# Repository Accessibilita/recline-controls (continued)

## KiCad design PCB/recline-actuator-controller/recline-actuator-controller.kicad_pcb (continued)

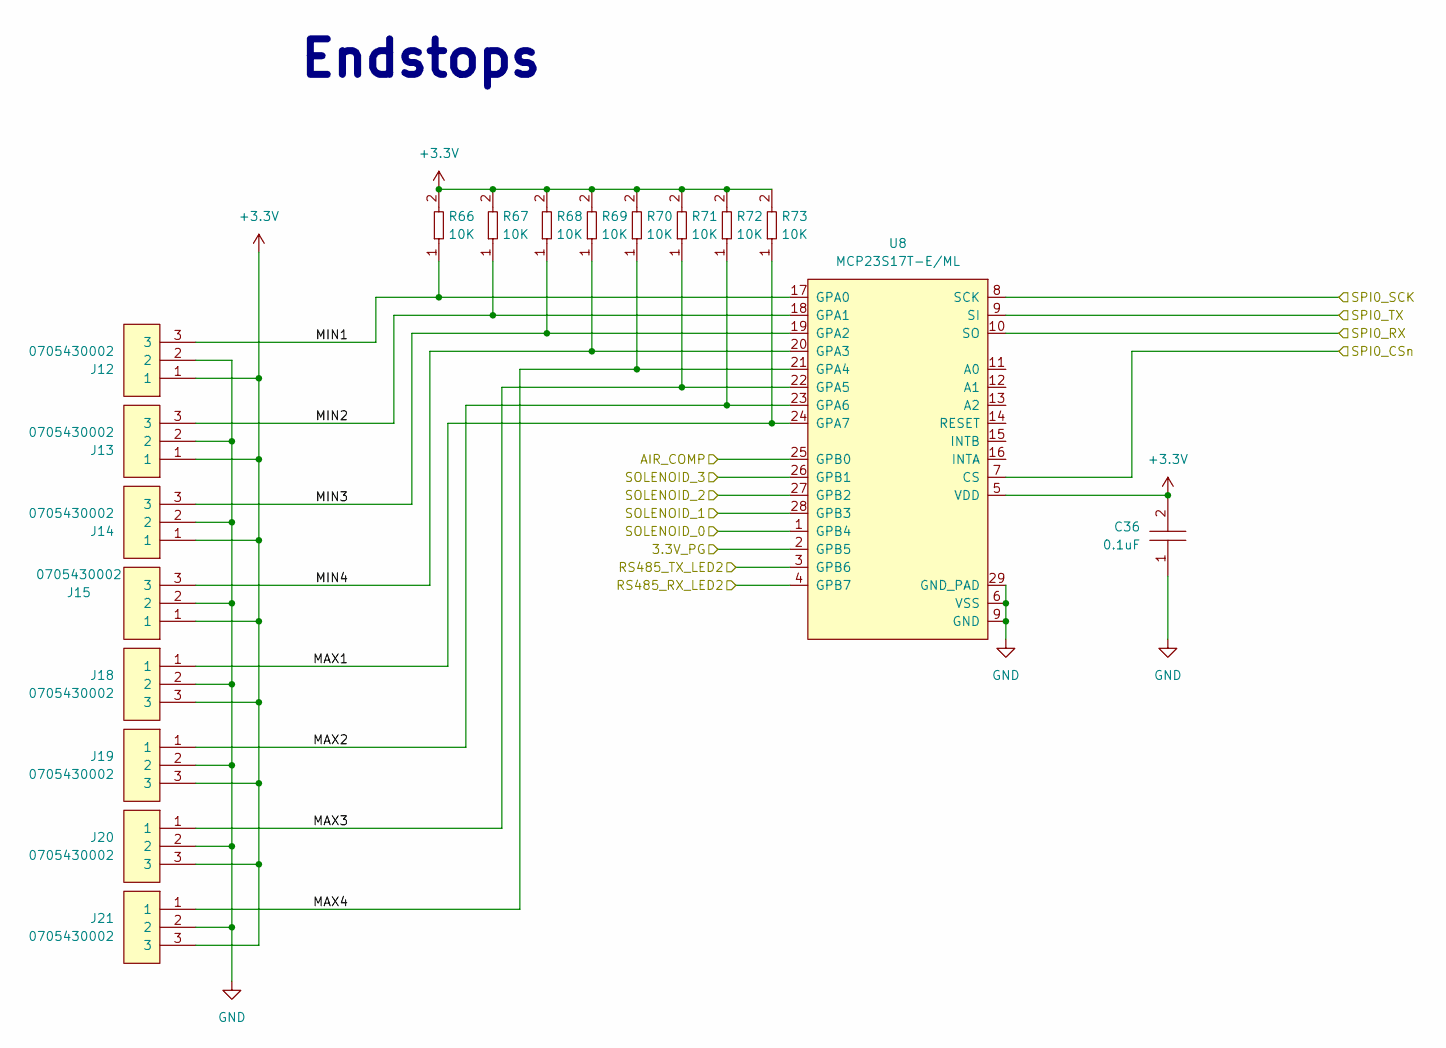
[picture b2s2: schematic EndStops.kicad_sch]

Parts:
C36: C0402C104K9PACTU; R0402; Tolerance 10%; Voltage 6.3V; MFR# C0402C104K9PACTU
J12, J13, J14, J15, J18, J19, J20, J21: 0705430002; Shrouded_Pin_Header_Straight_1x03_Pitch2.54mm; Tolerance *; Voltage 250V; MFR# 0705430002
R66, R67, R68, R69, R70, R71, R72, R73: RC0402FR-0710KL; R0402; Tolerance 1%; Voltage *; MFR# RC0402FR-0710KL
U8: MCP23S17T-E/ML; QFN28_6x6MC_MCH-L; Tolerance *; Voltage 1.8V-5.5V; MFR# MCP23S17T-E/ML

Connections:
+3.3V: C36.2, J12.1, J13.1, J14.1, J15.1, J18.3, J19.3, J20.3, J21.3, R66.2, R67.2, R68.2, R69.2, R70.2, R71.2, R72.2, R73.2, U8.5 (VDD); also elsewhere on the board
/End Stop Limit Switches/AIR_COMP: U8.25 (GPB0); also elsewhere on the board
/End Stop Limit Switches/MAX1: J18.1, R73.1, U8.24 (GPA7)
/End Stop Limit Switches/MAX2: J19.1, R72.1, U8.23 (GPA6)
/End Stop Limit Switches/MAX3: J20.1, R71.1, U8.22 (GPA5)
/End Stop Limit Switches/MAX4: J21.1, R70.1, U8.21 (GPA4)
/End Stop Limit Switches/MIN1: J12.3, R66.1, U8.17 (GPA0)
/End Stop Limit Switches/MIN2: J13.3, R67.1, U8.18 (GPA1)
/End Stop Limit Switches/MIN3: J14.3, R68.1, U8.19 (GPA2)
/End Stop Limit Switches/MIN4: J15.3, R69.1, U8.20 (GPA3)
/End Stop Limit Switches/RS485_RX_LED2: U8.4 (GPB7); also elsewhere on the board
/End Stop Limit Switches/RS485_TX_LED2: U8.3 (GPB6); also elsewhere on the board
/End Stop Limit Switches/SOLENOID_0: U8.1 (GPB4); also elsewhere on the board
/End Stop Limit Switches/SOLENOID_1: U8.28 (GPB3); also elsewhere on the board
/End Stop Limit Switches/SOLENOID_2: U8.27 (GPB2); also elsewhere on the board
/End Stop Limit Switches/SOLENOID_3: U8.26 (GPB1); also elsewhere on the board
/Power/3.3V_PG: U8.2 (GPB5); also elsewhere on the board
/RP2040/SPI0_CSn: U8.7 (CS); also elsewhere on the board
/RP2040/SPI0_RX: U8.10 (SO); also elsewhere on the board
/RP2040/SPI0_SCK: U8.8 (SCK); also elsewhere on the board

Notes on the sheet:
Endstops

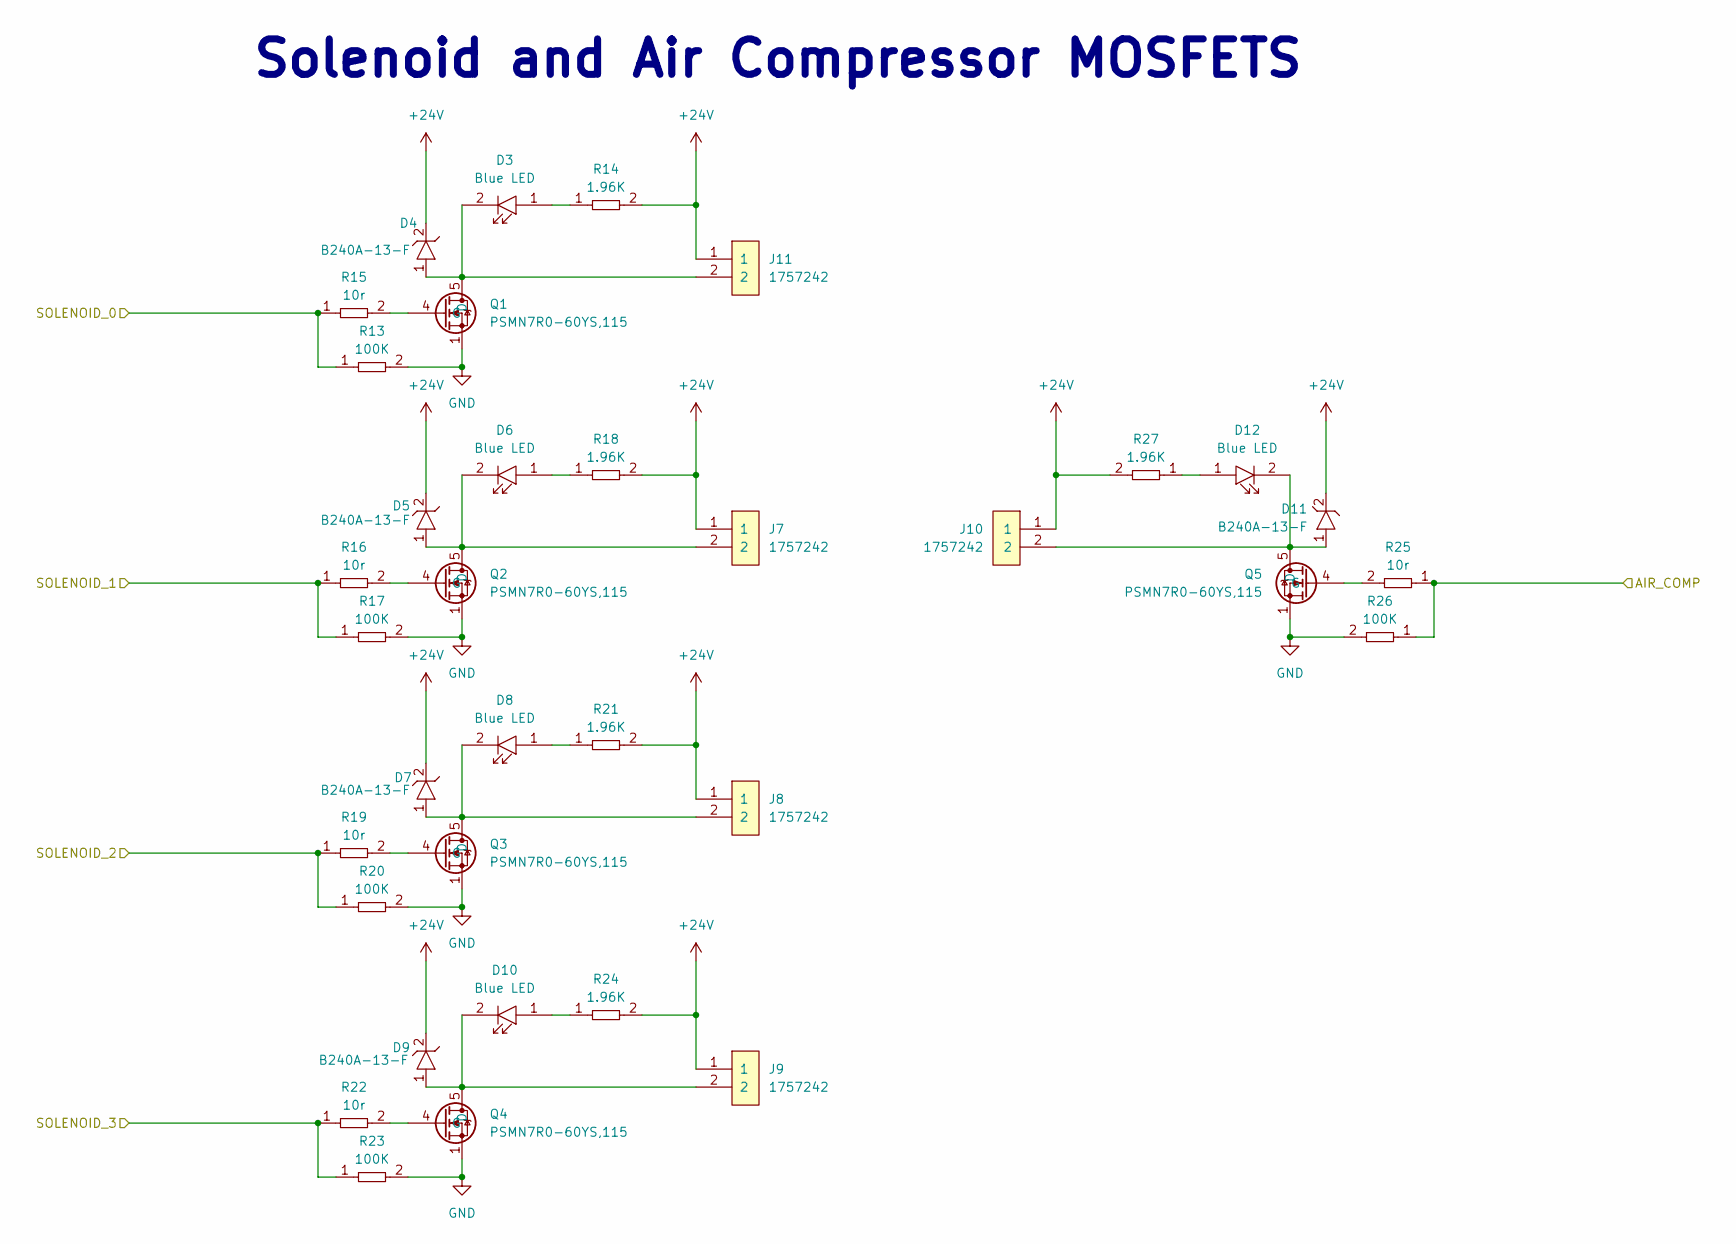
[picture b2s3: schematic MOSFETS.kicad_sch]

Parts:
D3, D6, D8, D10, D12: LTST-C194TBKT; LED0603; Tolerance *; Voltage 3.3V; MFR# LTST-C194TBKT
D4, D5, D7, D9, D11: B240A-13-F; Tolerance *; Voltage 40V; MFR# B240A-13-F
J7, J8, J9, J10, J11: 1757242; PhoenixContact_MSTBA-G_02x5.08mm_Angled; Tolerance *; Voltage 300V; MFR# 1757242
Q1, Q2, Q3, Q4, Q5: PSMN7R0-60YS,115; IC5_PSMN7R0-60YS_115_NEX-L; Tolerance *; Voltage 60V; MFR# PSMN7R0-60YS,115
R13, R17, R20, R23, R26: RC0805FR-07100KL; R0805; Tolerance 1%; Voltage *; MFR# RC0805FR-07100KL
R14, R18, R21, R24, R27: RC0805FR-071K96L; R0805; Tolerance 1%; Voltage N/A; MFR# RC0805FR-071K96L
R15, R16, R19, R22, R25: RC0805FR-0710RL; R0805; Tolerance 1%; Voltage *; MFR# RC0805FR-0710RL

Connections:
+24V: D4.2, D5.2, D7.2, D9.2, D11.2, J7.1, J8.1, J9.1, J10.1, J11.1, R14.2, R18.2, R21.2, R24.2, R27.2; also elsewhere on the board
/End Stop Limit Switches/AIR_COMP: R25.1, R26.1; also elsewhere on the board
/End Stop Limit Switches/SOLENOID_0: R13.1, R15.1; also elsewhere on the board
/End Stop Limit Switches/SOLENOID_1: R16.1, R17.1; also elsewhere on the board
/End Stop Limit Switches/SOLENOID_2: R19.1, R20.1; also elsewhere on the board
/End Stop Limit Switches/SOLENOID_3: R22.1, R23.1; also elsewhere on the board
unnamed: D3.1, R14.1
unnamed: D6.1, R18.1
unnamed: D8.1, R21.1
unnamed: D10.1, R24.1
unnamed: D12.1, R27.1
unnamed: D3.2, D4.1, J11.2, Q1.5 (D)
unnamed: Q1.4 (G), R15.2
unnamed: D5.1, D6.2, J7.2, Q2.5 (D)
unnamed: Q2.4 (G), R16.2
unnamed: D7.1, D8.2, J8.2, Q3.5 (D)
unnamed: Q3.4 (G), R19.2
unnamed: D9.1, D10.2, J9.2, Q4.5 (D)
unnamed: Q4.4 (G), R22.2
unnamed: D11.1, D12.2, J10.2, Q5.5 (D)
unnamed: Q5.4 (G), R25.2

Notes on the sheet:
Solenoid and Air Compressor MOSFETS

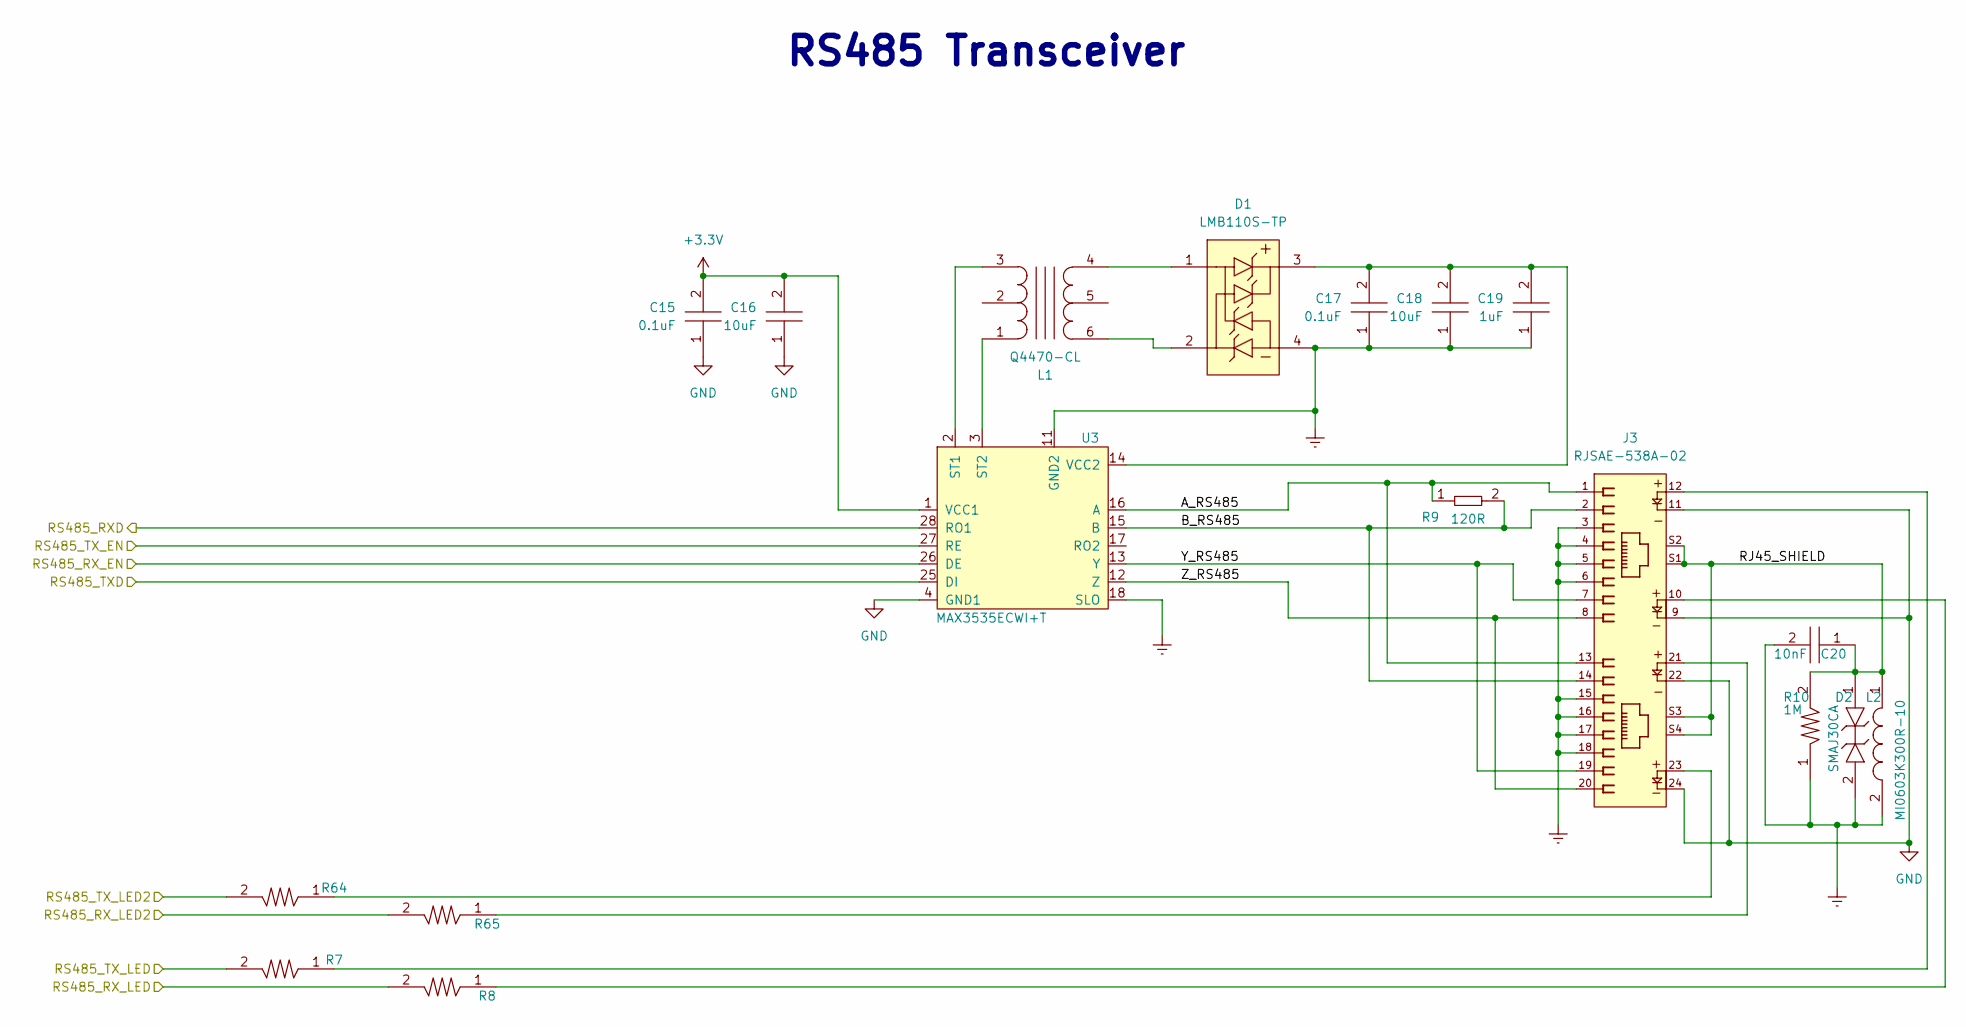
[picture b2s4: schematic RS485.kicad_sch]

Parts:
C15, C17: CL10B104JB8NNNC; C0603; Tolerance 5%; Voltage 50V; MFR# CL10B104JB8NNNC
C16, C18: CGA5L3X5R1V106K160AB; C1206; Tolerance 10%; Voltage 35V; MFR# CGA5L3X5R1V106K160AB
C19: C1206C105K3RACAUTO; D_SOD-123; Tolerance 10%; Voltage 25V; MFR# C1206C105K3RACAUTO
C20: C0805C103KCRACAUTO; C0805; Tolerance 10%; Voltage 500V; MFR# C0805C103KCRACAUTO
D1: LMB110S-TP; Tolerance *; Voltage 850 mV @ 500 mA; MFR# LMB110S-TP
D2: SMAJ30CA; Tolerance *; Voltage 30V Clamp; MFR# SMAJ30CA
J3: RJSAE-538A-02; AMPHENOL_RJSAE538A02; Tolerance N/A; Voltage *; MFR# RJSAE-538A-02
L1: Q4470-CL; SO6_Q4470-CL_C-SIZE_COC; Tolerance *; Voltage 5V; MFR# Q4470-CL
L2: MI0603K300R-10; Tolerance *; Voltage *; MFR# MI0603K300R-10
R7, R8, R64, R65: RC0603FR-07470RL; R0603; Tolerance 1%; Voltage *; MFR# RC0603FR-07470RL
R9: AC0402FR-07120RL; R0402; Tolerance 1%; Voltage *; MFR# AC0402FR-07120RL
R10: RC1206FR-071ML; R1206; Tolerance 1%; Voltage *; MFR# RC1206FR-071ML
U3: MAX3535ECWI+T; 21-0145_W28M&plus_9_MXM; Tolerance N/A; Voltage 3-5.5V; MFR# MAX3535ECWI+T

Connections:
+3.3V: C15.2, C16.2, U3.1 (VCC1); also elsewhere on the board
/End Stop Limit Switches/RS485_RX_LED2: R65.2; also elsewhere on the board
/End Stop Limit Switches/RS485_TX_LED2: R64.2; also elsewhere on the board
/RP2040/RS485_RXD: U3.28 (RO1); also elsewhere on the board
/RP2040/RS485_RX_EN: U3.26 (DE); also elsewhere on the board
/RP2040/RS485_RX_LED: R8.2; also elsewhere on the board
/RP2040/RS485_TXD: U3.25 (DI); also elsewhere on the board
/RP2040/RS485_TX_EN: U3.27 (RE); also elsewhere on the board
/RP2040/RS485_TX_LED: R7.2; also elsewhere on the board
/RS485 Transceiver/A_RS485: J3.1, J3.13, R9.1, U3.16 (A)
/RS485 Transceiver/B_RS485: J3.2, J3.14, R9.2, U3.15 (B)
/RS485 Transceiver/RJ45_SHIELD: C20.1, D2.1, J3.S1, J3.S2, J3.S3, J3.S4, L2.1, R10.2
/RS485 Transceiver/Y_RS485: J3.7, J3.19, U3.13 (Y)
/RS485 Transceiver/Z_RS485: J3.8, J3.20, U3.12 (Z)
Earth: C17.1, C18.1, C19.1, C20.2, D1.4, D2.2, J3.3, J3.4, J3.5, J3.6, J3.15, J3.16, J3.17, J3.18, L2.2, R10.1, U3.11 (GND2), U3.18 (SLO)
unnamed: D1.1, L1.4
unnamed: D1.2, L1.6
unnamed: J3.10, R8.1
unnamed: J3.12, R7.1
unnamed: J3.21, R65.1
unnamed: J3.23, R64.1
unnamed: L1.3, U3.2 (ST1)
unnamed: L1.1, U3.3 (ST2)
unnamed: C17.2, C18.2, C19.2, D1.3, U3.14 (VCC2)

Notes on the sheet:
RS485 Transceiver

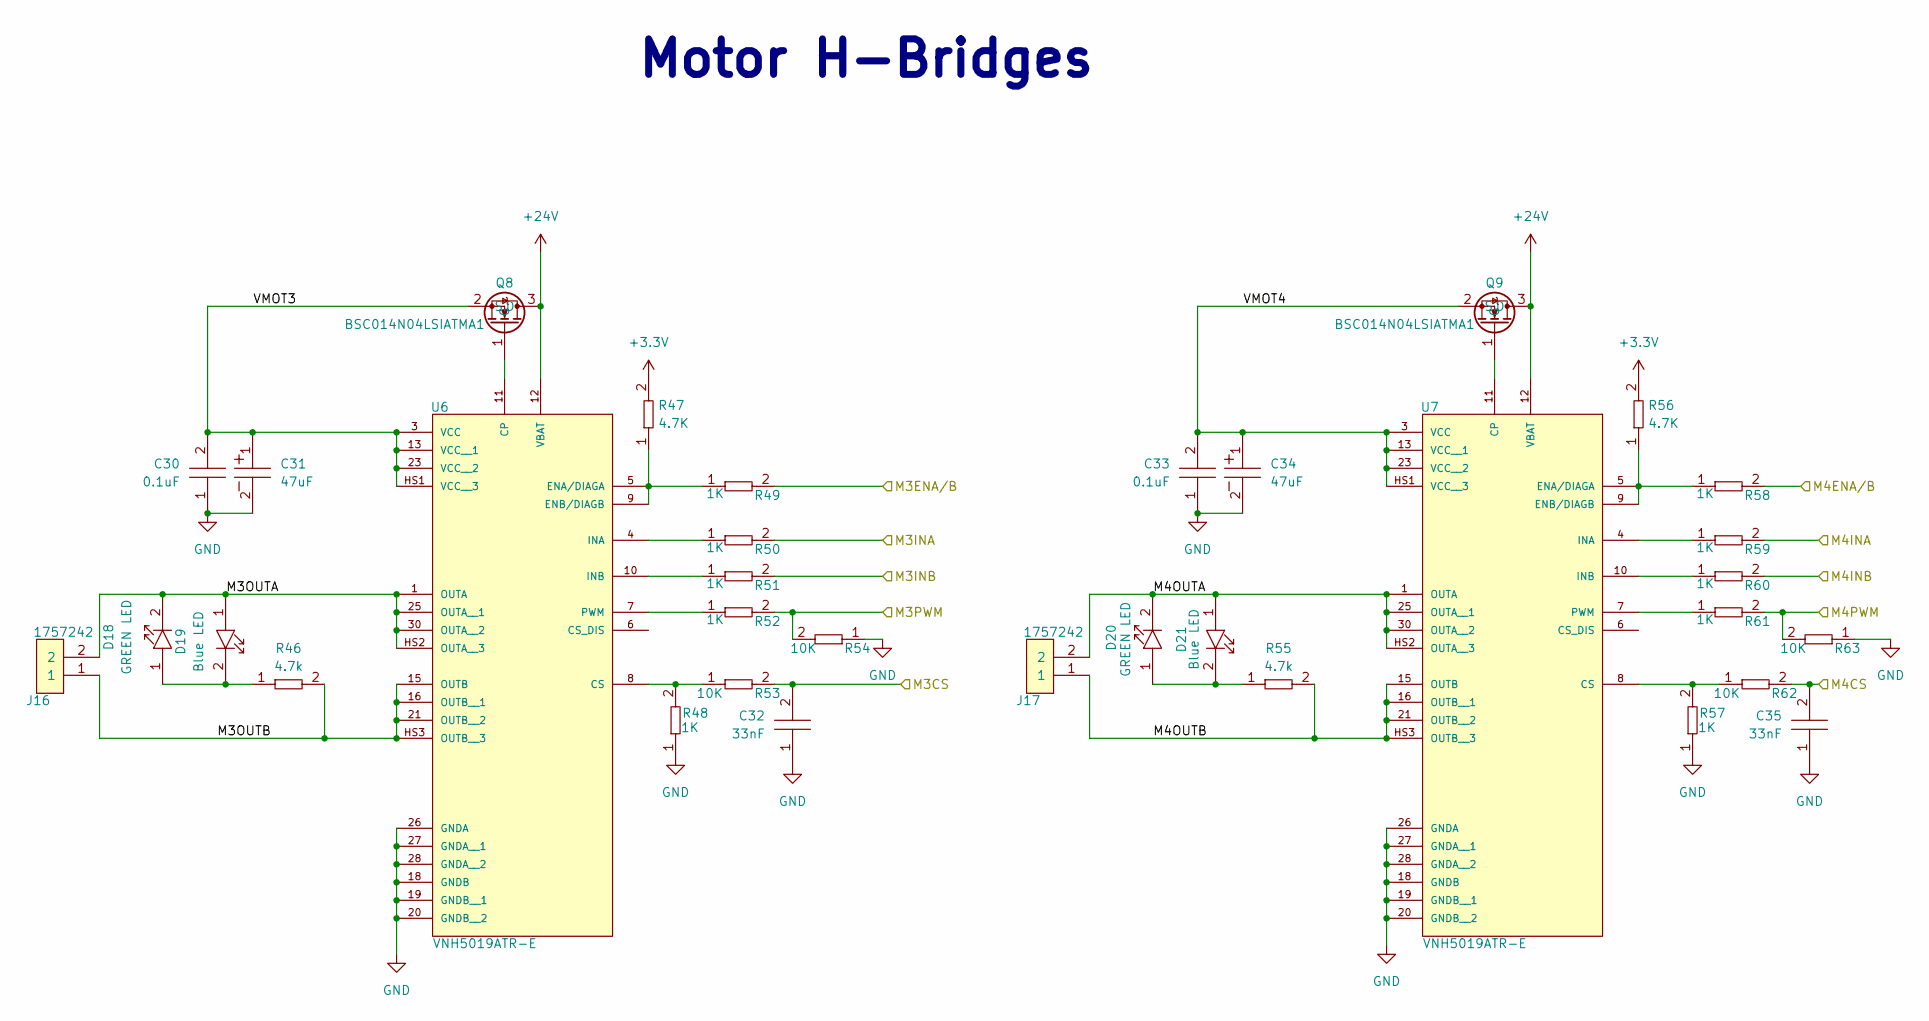
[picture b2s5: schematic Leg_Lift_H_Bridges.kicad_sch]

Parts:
C30, C33: CL21B104KBFNNNE; C0805; Tolerance 10%; Voltage 50V; MFR# Samsung Electro-Mechanics
C31, C34: UUQ1H470MCL1GS; CP_Elec_8x10; Tolerance 20%; Voltage 50V; MFR# UUQ1H470MCL1GS
C32, C35: C0402C333K4REC7867; C0402; Tolerance 10%; Voltage 16V; MFR# C0402C333K4REC7867
D18, D20: LTST-C194KGKT; LED0603; Tolerance *; Voltage 2.1V; MFR# LTST-C194KGKT
D19, D21: LTST-C194TBKT; LED0603; Tolerance *; Voltage 3.3V; MFR# LTST-C194TBKT
J16, J17: 1757242; PhoenixContact_MSTBA-G_02x5.08mm_Angled; Tolerance *; Voltage 300V; MFR# 1757242
Q8, Q9: BSC014N04LSIATMA1; PG-TDSON-8_INF; Tolerance N/A; Voltage 40V; MFR# BSC014N04LSIATMA1
R46, R55: RC0805FR-074K7L; R0805; Tolerance 1%; Voltage *; MFR# RC0805FR-074K7L
R47, R56: RC0402FR-074K7L; R0402; Tolerance 1%; Voltage *; MFR# RC0402FR-074K7L
R48, R49, R50, R51, R52, R57, R58, R59, R60, R61: RC0402FR-071KL; R0402; Tolerance 1%; Voltage *; MFR# RC0402FR-071KL
R53, R54, R62, R63: RC0402FR-0710KL; R0402; Tolerance 1%; Voltage *; MFR# RC0402FR-0710KL
U6, U7: VNH5019ATR-E; IC_VNH5019ATR-E; Tolerance *; Voltage 24; MFR# VNH5019ATR-E

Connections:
+3.3V: R47.2, R56.2; also elsewhere on the board
+24V: Q8.3 (D), Q9.3 (D), U6.12 (VBAT), U7.12 (VBAT); also elsewhere on the board
/Leg Lift Motors/M3CS: C32.2, R53.2; also elsewhere on the board
/Leg Lift Motors/M3ENA/B: R49.2; also elsewhere on the board
/Leg Lift Motors/M3INA: R50.2; also elsewhere on the board
/Leg Lift Motors/M3INB: R51.2; also elsewhere on the board
/Leg Lift Motors/M3OUTA: D18.2, D19.1, J16.2, U6.1 (OUTA), U6.25 (OUTA__1), U6.30 (OUTA__2), U6.HS2 (OUTA__3)
/Leg Lift Motors/M3OUTB: J16.1, R46.2, U6.15 (OUTB), U6.16 (OUTB__1), U6.21 (OUTB__2), U6.HS3 (OUTB__3)
/Leg Lift Motors/M3PWM: R52.2, R54.2; also elsewhere on the board
/Leg Lift Motors/M4CS: C35.2, R62.2; also elsewhere on the board
/Leg Lift Motors/M4ENA/B: R58.2; also elsewhere on the board
/Leg Lift Motors/M4INA: R59.2; also elsewhere on the board
/Leg Lift Motors/M4INB: R60.2; also elsewhere on the board
/Leg Lift Motors/M4OUTA: D20.2, D21.1, J17.2, U7.1 (OUTA), U7.25 (OUTA__1), U7.30 (OUTA__2), U7.HS2 (OUTA__3)
/Leg Lift Motors/M4OUTB: J17.1, R55.2, U7.15 (OUTB), U7.16 (OUTB__1), U7.21 (OUTB__2), U7.HS3 (OUTB__3)
/Leg Lift Motors/M4PWM: R61.2, R63.2; also elsewhere on the board
/Leg Lift Motors/VMOT3: C30.2, C31.1, Q8.2 (S), U6.3 (VCC), U6.13 (VCC__1), U6.23 (VCC__2), U6.HS1 (VCC__3)
/Leg Lift Motors/VMOT4: C33.2, C34.1, Q9.2 (S), U7.3 (VCC), U7.13 (VCC__1), U7.23 (VCC__2), U7.HS1 (VCC__3)
unnamed: D18.1, D19.2, R46.1
unnamed: D20.1, D21.2, R55.1
unnamed: Q8.1 (G), U6.11 (CP)
unnamed: Q9.1 (G), U7.11 (CP)
unnamed: R48.2, R53.1, U6.8 (CS)
unnamed: R47.1, R49.1, U6.5 (ENA/DIAGA), U6.9 (ENB/DIAGB)
unnamed: R50.1, U6.4 (INA)
unnamed: R51.1, U6.10 (INB)
unnamed: R52.1, U6.7 (PWM)
unnamed: R57.2, R62.1, U7.8 (CS)
unnamed: R56.1, R58.1, U7.5 (ENA/DIAGA), U7.9 (ENB/DIAGB)
unnamed: R59.1, U7.4 (INA)
unnamed: R60.1, U7.10 (INB)
unnamed: R61.1, U7.7 (PWM)

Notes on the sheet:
Motor H-Bridges

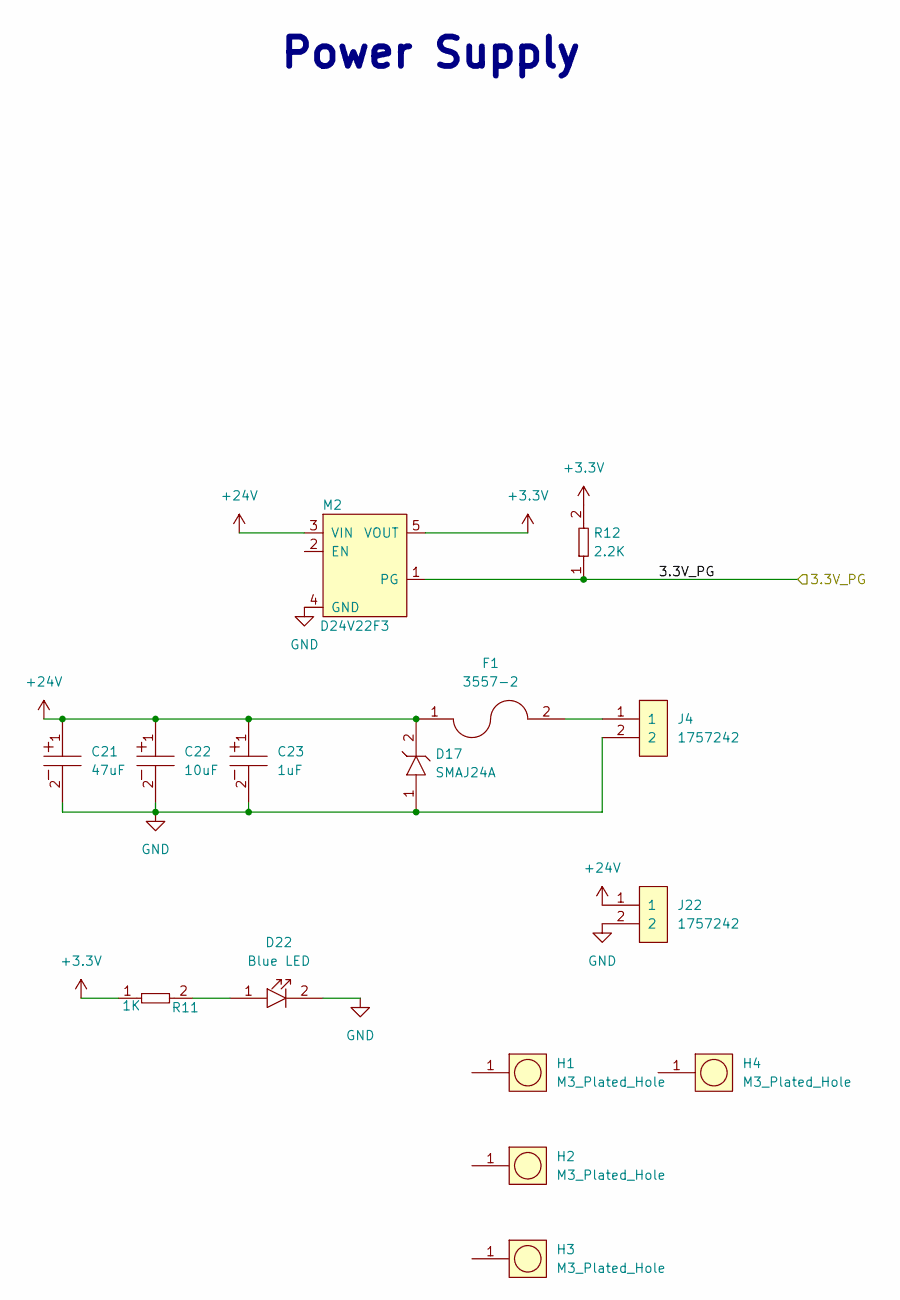
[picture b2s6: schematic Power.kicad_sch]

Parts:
C21: UUQ1H470MCL1GS; CP_Elec_8x10; Tolerance 20%; Voltage 50V; MFR# UUQ1H470MCL1GS
C22: UUQ1H100MCL1GB; CP_Elec_4x5.3; Tolerance 20%; Voltage 50V; MFR# UUQ1H100MCL1GB
C23: UUQ1H010MCL1GB; CP_Elec_4x5.3; Tolerance 20%; Voltage 50V; MFR# UUQ1H010MCL1GB
D17: SMAJ24A; SMAJ; Tolerance *; Voltage 24V RS, 26.7V VB, 38.9V Clamp; MFR# SMAJ24A
D22: LTST-C194TBKT; LED0603; Tolerance *; Voltage 3.3V; MFR# LTST-C194TBKT
F1: 3557-2; FUSE_3557-2; Tolerance *; Voltage 500V; MFR# 3557-2
H1, H2, H3, H4: M3_Plated_Hole; M3_HOLE; Tolerance *; Voltage *; MFR# *
J4, J22: 1757242; PhoenixContact_MSTBA-G_02x5.08mm_Angled; Tolerance *; Voltage 300V; MFR# 1757242
M2: D24V22F3; D24V22F12; Tolerance N/A; Voltage 36V IN 3.3V OUT; MFR# D24V22F3
R11: RC0402FR-071KL; R0402; Tolerance 1%; Voltage *; MFR# RC0402FR-071KL
R12: RC0603FR-072K2L; R0603; Tolerance 1%; Voltage N/A; MFR# RC0603FR-072K2L

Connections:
+3.3V: M2.5 (VOUT), R11.1, R12.2; also elsewhere on the board
+24V: C21.1, C22.1, C23.1, D17.2, F1.1, J22.1, M2.3 (VIN); also elsewhere on the board
/Power/3.3V_PG: M2.1 (PG), R12.1; also elsewhere on the board
unnamed: D22.1, R11.2
unnamed: F1.2, J4.1

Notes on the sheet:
Power Supply

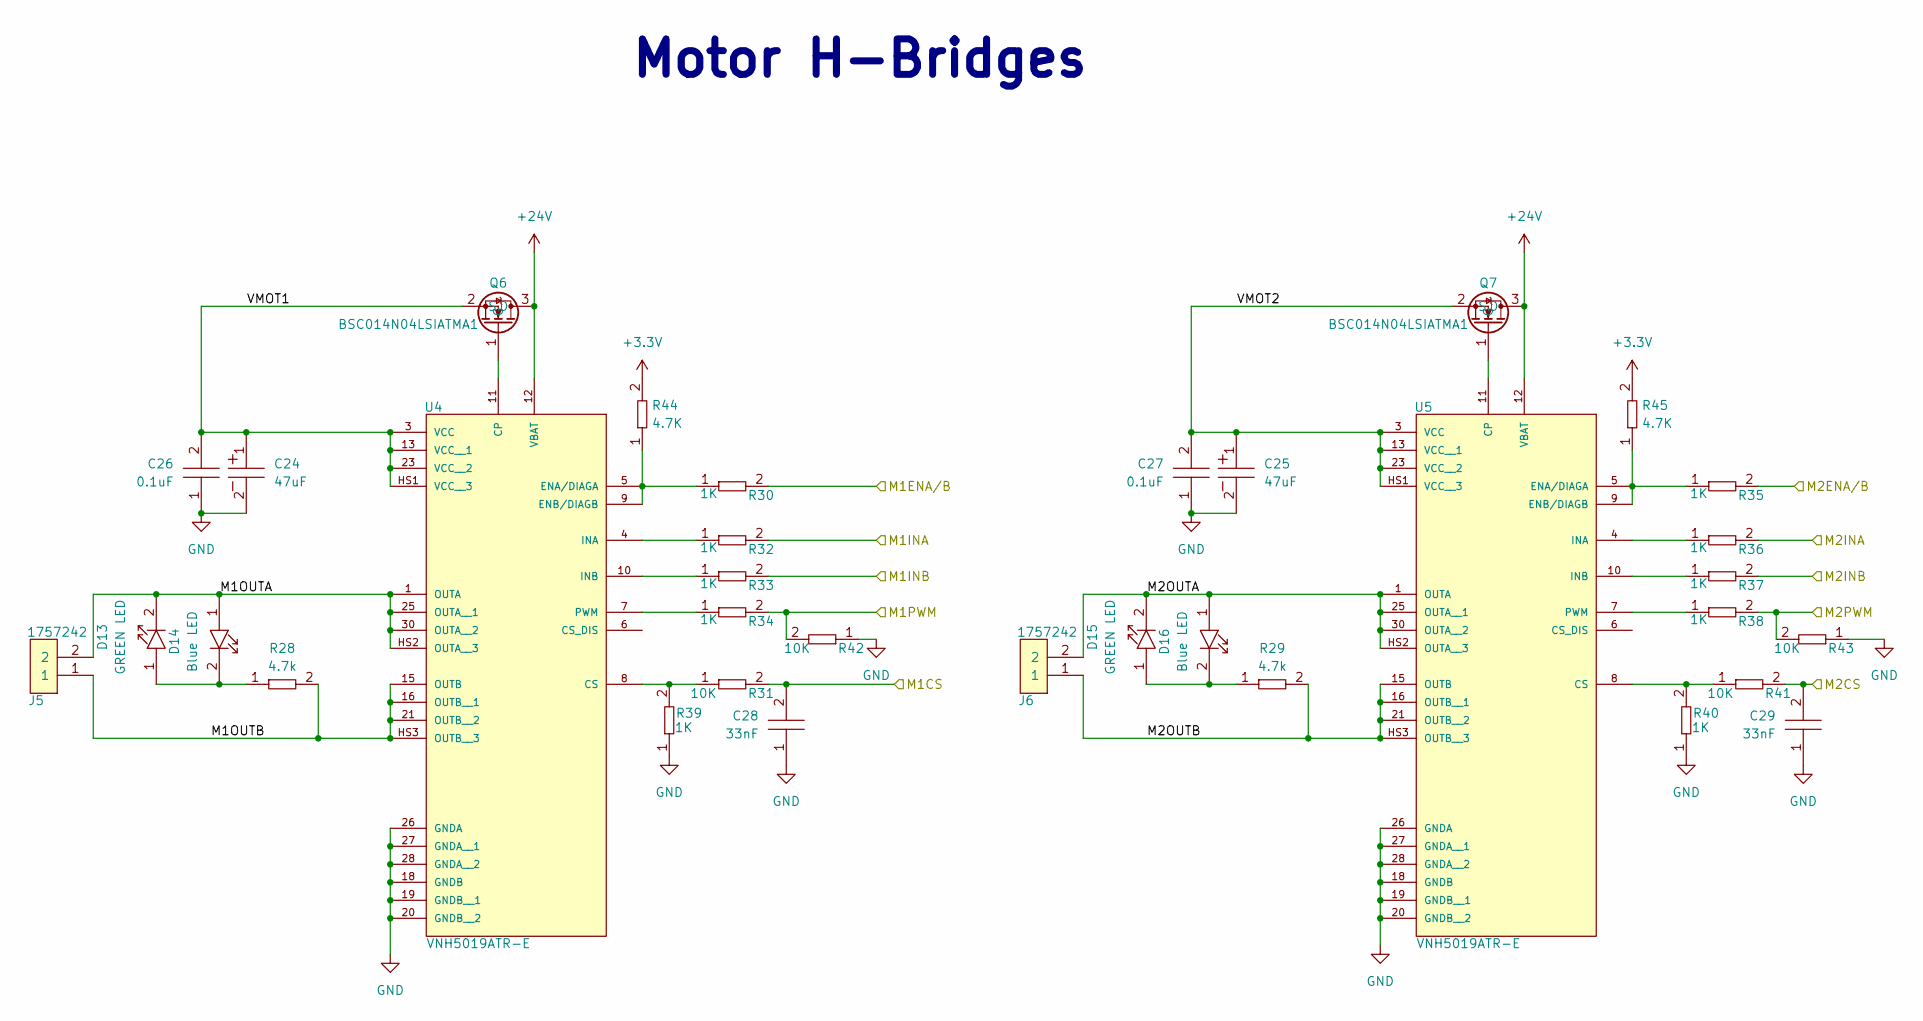
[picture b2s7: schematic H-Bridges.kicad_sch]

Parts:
C24, C25: UUQ1H470MCL1GS; CP_Elec_8x10; Tolerance 20%; Voltage 50V; MFR# UUQ1H470MCL1GS
C26, C27: CL21B104KBFNNNE; C0805; Tolerance 10%; Voltage 50V; MFR# Samsung Electro-Mechanics
C28, C29: C0402C333K4REC7867; C0402; Tolerance 10%; Voltage 16V; MFR# C0402C333K4REC7867
D13, D15: LTST-C194KGKT; LED0603; Tolerance *; Voltage 2.1V; MFR# LTST-C194KGKT
D14, D16: LTST-C194TBKT; LED0603; Tolerance *; Voltage 3.3V; MFR# LTST-C194TBKT
J5, J6: 1757242; PhoenixContact_MSTBA-G_02x5.08mm_Angled; Tolerance *; Voltage 300V; MFR# 1757242
Q6, Q7: BSC014N04LSIATMA1; PG-TDSON-8_INF; Tolerance N/A; Voltage 40V; MFR# BSC014N04LSIATMA1
R28, R29: RC0805FR-074K7L; R0805; Tolerance 1%; Voltage *; MFR# RC0805FR-074K7L
R30, R32, R33, R34, R35, R36, R37, R38, R39, R40: RC0402FR-071KL; R0402; Tolerance 1%; Voltage *; MFR# RC0402FR-071KL
R31, R41, R42, R43: RC0402FR-0710KL; R0402; Tolerance 1%; Voltage *; MFR# RC0402FR-0710KL
R44, R45: RC0402FR-074K7L; R0402; Tolerance 1%; Voltage *; MFR# RC0402FR-074K7L
U4, U5: VNH5019ATR-E; IC_VNH5019ATR-E; Tolerance *; Voltage 24; MFR# VNH5019ATR-E

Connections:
+3.3V: R44.2, R45.2; also elsewhere on the board
+24V: Q6.3 (D), Q7.3 (D), U4.12 (VBAT), U5.12 (VBAT); also elsewhere on the board
/Motor H-Bridges/M1CS: C28.2, R31.2; also elsewhere on the board
/Motor H-Bridges/M1ENA/B: R30.2; also elsewhere on the board
/Motor H-Bridges/M1INA: R32.2; also elsewhere on the board
/Motor H-Bridges/M1INB: R33.2; also elsewhere on the board
/Motor H-Bridges/M1OUTA: D13.2, D14.1, J5.2, U4.1 (OUTA), U4.25 (OUTA__1), U4.30 (OUTA__2), U4.HS2 (OUTA__3)
/Motor H-Bridges/M1OUTB: J5.1, R28.2, U4.15 (OUTB), U4.16 (OUTB__1), U4.21 (OUTB__2), U4.HS3 (OUTB__3)
/Motor H-Bridges/M1PWM: R34.2, R42.2; also elsewhere on the board
/Motor H-Bridges/M2CS: C29.2, R41.2; also elsewhere on the board
/Motor H-Bridges/M2ENA/B: R35.2; also elsewhere on the board
/Motor H-Bridges/M2INA: R36.2; also elsewhere on the board
/Motor H-Bridges/M2INB: R37.2; also elsewhere on the board
/Motor H-Bridges/M2OUTA: D15.2, D16.1, J6.2, U5.1 (OUTA), U5.25 (OUTA__1), U5.30 (OUTA__2), U5.HS2 (OUTA__3)
/Motor H-Bridges/M2OUTB: J6.1, R29.2, U5.15 (OUTB), U5.16 (OUTB__1), U5.21 (OUTB__2), U5.HS3 (OUTB__3)
/Motor H-Bridges/M2PWM: R38.2, R43.2; also elsewhere on the board
/Motor H-Bridges/VMOT1: C24.1, C26.2, Q6.2 (S), U4.3 (VCC), U4.13 (VCC__1), U4.23 (VCC__2), U4.HS1 (VCC__3)
/Motor H-Bridges/VMOT2: C25.1, C27.2, Q7.2 (S), U5.3 (VCC), U5.13 (VCC__1), U5.23 (VCC__2), U5.HS1 (VCC__3)
unnamed: D13.1, D14.2, R28.1
unnamed: D15.1, D16.2, R29.1
unnamed: Q6.1 (G), U4.11 (CP)
unnamed: Q7.1 (G), U5.11 (CP)
unnamed: R31.1, R39.2, U4.8 (CS)
unnamed: R30.1, R44.1, U4.5 (ENA/DIAGA), U4.9 (ENB/DIAGB)
unnamed: R32.1, U4.4 (INA)
unnamed: R33.1, U4.10 (INB)
unnamed: R34.1, U4.7 (PWM)
unnamed: R40.2, R41.1, U5.8 (CS)
unnamed: R35.1, R45.1, U5.5 (ENA/DIAGA), U5.9 (ENB/DIAGB)
unnamed: R36.1, U5.4 (INA)
unnamed: R37.1, U5.10 (INB)
unnamed: R38.1, U5.7 (PWM)

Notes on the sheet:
Motor H-Bridges

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
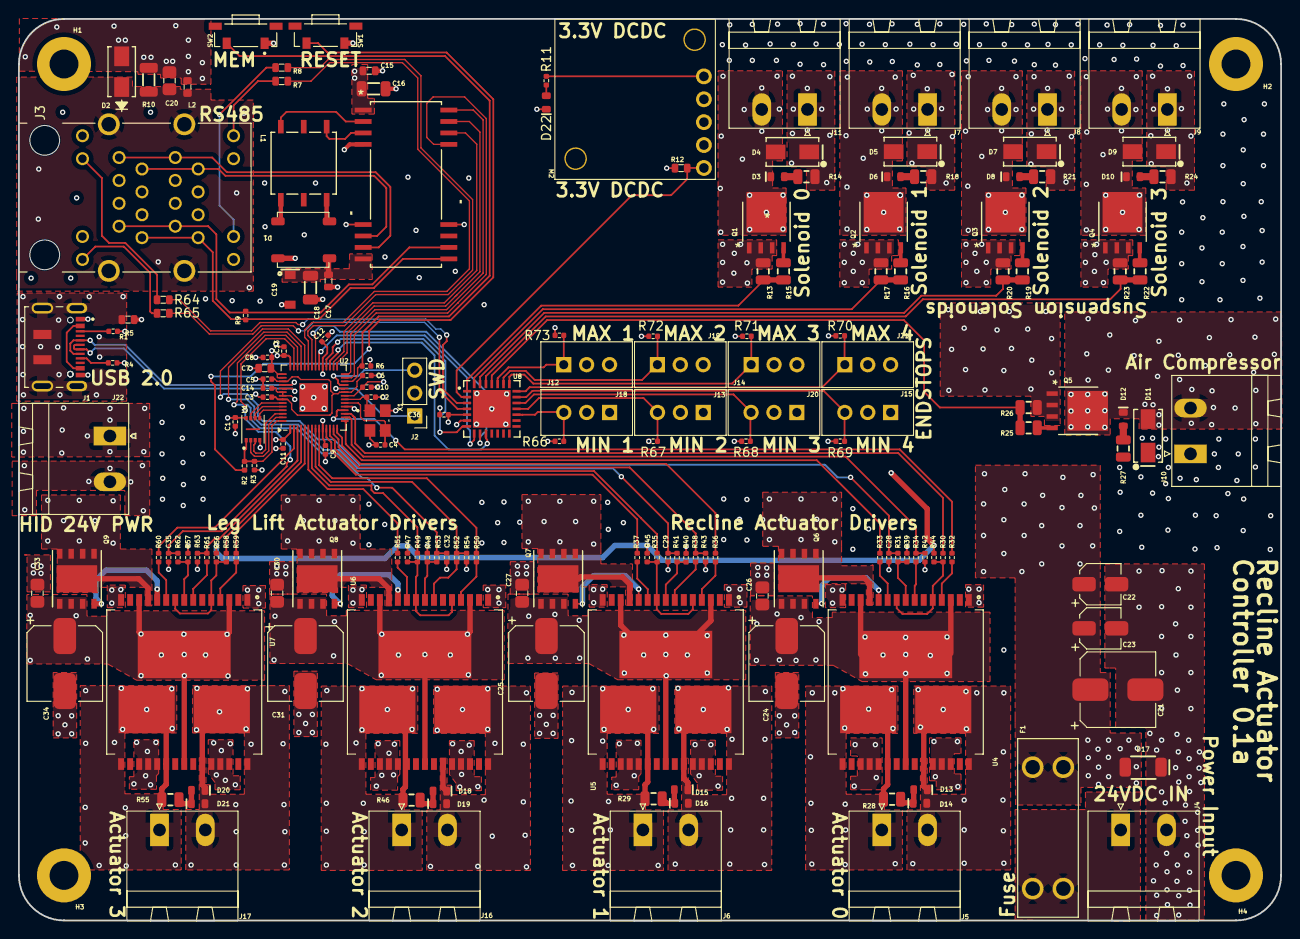
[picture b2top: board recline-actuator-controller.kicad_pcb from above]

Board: 4 copper layers, 140.0 x 100.0 mm, 181 parts (0 on the bottom side), 140 nets.

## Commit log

2024-07-12 Projects Created and Schematics Started
    Devised a complete architecture for chair recline system controls after consulting with Matt Lacey. System split across two boards. One board will function as controller, interfacing with switches/7S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
2024-07-15 Recline Actuator Control
    Recline controller board schematic and Recline actuator board schematics. Actuator control board schematic 90% complete.
2024-07-15 Actuator Control Schematic
    Schematic for Actuator control board completed! Once reviewed PCB layout will start.
2024-07-15 Recline Controls
    Recline Control board and human machine interface board schematic complete !
2024-07-15 7 Segment Carrier
    Created project and schematic for 7 segment display carrier board. It needs to be mounted at a right angle and there are no right angle 7 segment displays on the market so it will be mounted to a car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
2024-07-16 Read Me
    Updated readme with description of boards and their function with block diagram.
2024-07-16 Update README.md
    Formatting
2024-07-16 Update README.md
    more formatting
2024-07-22 PCB Started
    PCB design for Recline Control Board started, figuring out PCB shape and connector positioning, work in progress !
2024-07-22 Recline Actuator Control PCB
    Recline Actuator Control PCB created. Still need to figure out board shape and connector placement.
2024-07-23 Connectors
    Datasheet for IP67 connectors added
2024-07-24 Actuator Control Board MOSFET
    Swapped Actuator control board MOSFET over to a more thermally efficient part
2024-08-03 Switching Workstations
    Syncing progress for switching to mobile workstation
2024-09-24 PCB shape and Layout
    PCB shape defined, parts placed 90% layout in progress.
2024-09-24 PCB Layout Progress
    Lots of progress made on PCB layout, MOSFET section complete, H-Bridges in progress, lots of work done and lots more to do, 3 copper layers are being utilized to provide ample copper for carrying all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
2024-09-30 Actuator Control Board - RP2040
    RP2040 section routed on Actuator control board !
2024-10-05 First Pass of PCB
    First pass of PCB complete, needs review.
2024-11-02 All Hardware Tweaked / 3D Renders
    PCBs for Actuator Control, Recline Control HID, and 7 Segment carrier are all complete with full 3D models rendering. 3D Renders of all board added to repository img directory.
2024-11-02 Update README.md
    First update to read me ! Added 3D renders for both boards, reorganized order of read me images and text.
2024-11-02 Update README.md
    Recline actuator controller board description updated
2024-11-02 Update README.md
    Recline Control Board descirption updated
2024-11-02 ISO and 2D Renders
    ISO 3D renders of Actuator board
2024-11-02 Update README.md
    Added 2D renders of boards
2024-11-02 Update README.md
    Added ISO 3D renders of actuator controller board, and tweaked specs for both boards to reflect new features.
2024-11-06 More Motor Channels
    Adding more motor channels to actuator control board it will need new MCU or port expansion.
2024-12-17 Recline Actuator Board Redesign
    Recline actuator control board redesign complete, functionality extended to handle two additional large actuators for leg lifting. Air compressor switching circuit made to handle higher current. Addi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
2024-12-18 RS485
    RS485 schematic corrected, 5V regulator removed.
2024-12-21 RS485
    RS485 circuit fixed and PCB topology updated.
2024-12-28 Via Stichign and Pullups
    Added optional pullups to endstop circuit. Revised via stitching for input power, revised layout with added via stitching and copper pours for solenoid mosfets.
2024-12-30 HID
    Changes made to recline control HID board. Power input section redesigned, 5V regulator removed, RS485 circuit updated with fixes that other boards received. Redesign or internal plane topology follo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
2024-12-31 Powerplane
    Recline actuator controller power plane topology modified and upgraded
2025-01-01 Documentation
    Updated renders
2025-01-09 3D Models
    3D Models of circuit boards generated and added to project.
2025-01-10 Board Pinout Tables
    Pinout charts for RP2040 Pin connections and signal functions added to main repo directory.
2025-01-13 PDF Schematics
    PDFs of schematics added for firmware developers
2025-03-11 Silkscreen
    Bottom Silkscreen edits.
